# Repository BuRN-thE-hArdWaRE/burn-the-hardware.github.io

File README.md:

# E-01 Drive

This repository contains the documentation and design package for `E-01 Drive`, a hardware platform built to make PID tuning easier on real systems. The current prototype is a compact self-balancing robot style control platform built around an ESP32-S3, MPU-6050, motor driver, OLED, battery power stage, custom PCB, and mechanical chassis.

## 1. Title of the Project

`E-01 Drive: AI-Assisted PID Tuning Platform for a Self-Balancing Robot`

## 2. Problem Statement

PID controllers are widely used in robotics and embedded systems, but tuning them on real hardware is still difficult. In most student and prototype projects, tuning is done by manual trial-and-error. This wastes time, increases instability during testing, and makes it hard to reach a reliable operating point quickly.

For a self-balancing robot, the problem becomes even harder because small changes in gains can produce oscillation, overshoot, or immediate failure. A practical system is needed that can reduce the effort of selecting good PID gains while still working on real hardware.

## 3. Objective

The objective of E-01 Drive is to simplify and accelerate PID tuning by combining:

- a real embedded hardware platform,
- live sensing and motor actuation,
- a structured tuning workflow,
- and an AI-assisted tuning engine that can suggest updated gains from measured hardware responses.

The project aims to reduce manual tuning effort while improving repeatability, speed of iteration, and clarity during testing.

## 4. Existing Work

The project builds on the following common approaches already used in control engineering and robotics:

- Manual PID tuning by observing overshoot, settling time, and steady-state error.
- Classical heuristics such as Ziegler-Nichols style gain estimation.
- Simulation-first controller development before real hardware deployment.
- Adaptive and learning-based tuning methods explored in academic and industrial control systems.
- Reinforcement learning approaches for automatic controller optimization.

Within this project itself, an earlier software approach attempted TD3-based reinforcement learning for automatic PID tuning across simulated systems, but it did not produce reliable enough results for deployment on the real robot.

## 5. Gap Analysis

Existing PID tuning approaches still leave several gaps for student-built real hardware systems:

- Manual tuning is slow and highly dependent on user experience.
- Classical formulas are often too coarse for unstable or nonlinear platforms like self-balancing robots.
- Simulation-only results do not always transfer well to real hardware.
- Reinforcement learning methods can be complex to train and may fail to generalize reliably.
- Many systems do not provide a simple end-to-end workflow that connects hardware measurements directly to gain recommendations.

This gap creates a need for a practical platform that combines real hardware experimentation with a smarter iterative tuning process.

## 6. Novelty

The novelty of E-01 Drive is the combination of:

- a real self-balancing robot style hardware platform,
- a custom PCB for integrating sensing, control, motor drive, and power,
- and an AI-assisted tuning loop that uses measured hardware response data to guide PID updates.

Rather than treating PID tuning as a one-time manual setup step, the project treats tuning as an iterative data-driven workflow with both offline and online phases. This makes the prototype different from a simple balancing bot or a standard fixed-gain controller demo.

## 7. Your Project Description

E-01 Drive is a compact embedded hardware platform designed to evaluate and improve PID tuning on a real robotic system. The prototype uses:

- an ESP32-S3 development board as the main controller,
- an MPU-6050 IMU for motion sensing,
- a dual motor driver to control the two drive motors,
- an OLED display for local status output,
- a DC-DC module and battery-powered supply chain,
- a custom PCB to organize the electronics,
- and a two-wheel chassis suitable for balancing and motion-control experiments.

The control workflow is built around a self-balancing robot use case. The robot measures tilt and motion, applies PID control through the motors, and records system behavior. An external tuning service can then analyze the response and suggest better gain values. This creates a tighter loop between observation, tuning, testing, and retesting.

## 8. List of Components and the Software Used

### Hardware Components

| Component | Purpose |
| --- | --- |
| ESP32-S3 board | Main microcontroller and control execution |
| MPU-6050 IMU | Tilt and motion feedback |
| Motor driver module | Drives the left and right DC motors |
| OLED display | Local status and tuning output |
| DC-DC converter | Voltage regulation |
| Toggle switch | Power control |
| 3.7V 1200mAh battery | Portable power source |
| Two TT gear motors | Actuation |
| Two wheels | Locomotion and balance support |
| Custom PCB | Interconnect and integration platform |
| Mechanical chassis/body | Prototype structure |

### Software and Tools Used

| Software / Tool | Purpose |
| --- | --- |
| KiCad 9 | Schematic and PCB design |
| Gerber export tools | Manufacturing output generation |
| FastAPI | Backend service for tuning workflow |
| Cloud LLM tuner | Gain recommendation and adaptive tuning logic |
| SvelteKit website repo | Public project presentation and documentation |
| STEP / STL / GLB exports | 3D model sharing and fabrication references |

## 9. Methodology

The project methodology combines hardware design, embedded control, and AI-assisted tuning:

1. Design and fabricate a compact PCB for the controller, IMU, motor driver, and power modules.
2. Assemble a robot platform with two motors, wheels, battery supply, and control electronics.
3. Read tilt and motion data from the IMU using the controller.
4. Run a PID-based control loop on the hardware platform.
5. Perform exploratory hardware runs to collect response metrics.
6. Use measured values such as settling time, overshoot, steady-state error, and stability to guide gain updates.
7. Iterate until the system reaches improved behavior.

The broader tuning concept is divided into:

- `Offline tuning`: structured initial tuning using exploratory runs and recorded results.
- `Online tuning`: adaptive updates based on new disturbances or live system behavior.

## 10. Work Flow

The current project workflow can be described as:

1. Power the robot through the battery, switch, and DC-DC stage.
2. Read angle and motion feedback from the MPU-6050.
3. Execute the control loop on the ESP32-S3.
4. Drive the motors through the motor driver.
5. Observe system behavior on the hardware platform.
6. Record response metrics from each trial.
7. Send the results to the tuning workflow.
8. Receive improved PID gains.
9. Re-apply the gains on hardware and repeat.

The software architecture currently described for the tuning engine includes:

- `/init_session`
- `/answer_questions`
- `/send_results`
- `/accept`
- `/start_adaptive`
- `/breach`

These endpoints represent the offline and adaptive tuning phases of the project.

### Tuning Progress Graphs

The following graphs summarize the tuning behavior shared for this project. These repository assets were recreated from the graph screenshots provided during documentation so they can be embedded directly in the public README.

#### Kp Over Iterations

#### Steady State Over Iterations

#### Overshoot Trend During Tuning

#### PID Gains Over Iterations

## 11. Pic of the Project / Prototype

### Assembled Prototype

### Custom PCB

### Chassis and Motors

## 12. Demo Video

Software demo video file available locally: `2026-04-12 14-31-13.mkv`

Important note: the provided video file is approximately 177 MB, which exceeds GitHub's normal 100 MB file-size limit for repository commits. To complete the final submission cleanly, this video should be uploaded to a public hosting platform such as YouTube or Google Drive, and that public link should be placed here before judging.

## 13. Public GitHub Repo Deliverables

Public repository: [BuRN-thE-hArdWaRE/burn-the-hardware.github.io](https://github.com/BuRN-thE-hArdWaRE/burn-the-hardware.github.io)

### Schematics and Circuit Design

- [KiCad schematic](hardware/kicad/E-01%20Drive.kicad_sch)
- [KiCad project file](hardware/kicad/E-01%20Drive.kicad_pro)

Note: the current schematic file exists in the repository, but it is still largely incomplete and should be finished for a fully reproducible hardware submission.

### PCB Layout (KiCad Project File)

- [PCB layout](hardware/kicad/E-01%20Drive.kicad_pcb)
- [KiCad project](hardware/kicad/E-01%20Drive.kicad_pro)

### Gerber File

- [Gerber folder](hardware/gerber/team5_gerber_x2/)
- [Gerber ZIP package](hardware/gerber/team5_gerber_x2/team-5_gerber.zip)

### Source Code

- [Website source](src/)
- [Firmware and tuning architecture note](firmware/README.md)

Important note: actual firmware source files were not present in the local workspace provided for this update. This repository now includes the firmware architecture description, but the embedded source code should still be added if you want the submission to include the full software implementation.

### 3D Model With Specifications

- [STEP model](hardware/models/E-01%20Drive.step)
- [STL model](hardware/models/E-01%20Drive.stl)
- [GLB model](hardware/models/E-01%20Drive.glb)

These files provide the current 3D representation of the mechanical and hardware package available in the workspace.

## Firmware and Tuning Architecture Summary

The current tuning architecture is based on a hybrid control workflow:

- the ESP32-S3 executes the live control loop on the robot,
- the MPU-6050 provides motion feedback,
- the motor driver applies actuator output,
- and an external AI-assisted tuning service recommends PID gains from observed hardware results.

An earlier TD3 reinforcement learning approach was explored and later abandoned due to unreliable performance for real-world deployment. The current approach uses a cloud LLM with a FastAPI-based session workflow for offline and online gain adjustment.

Additional firmware notes are available in [firmware/README.md](firmware/README.md).

## Additional Project Images

### OLED Module

### IMU Module

### Motor Driver

### Power Section

### Wheels

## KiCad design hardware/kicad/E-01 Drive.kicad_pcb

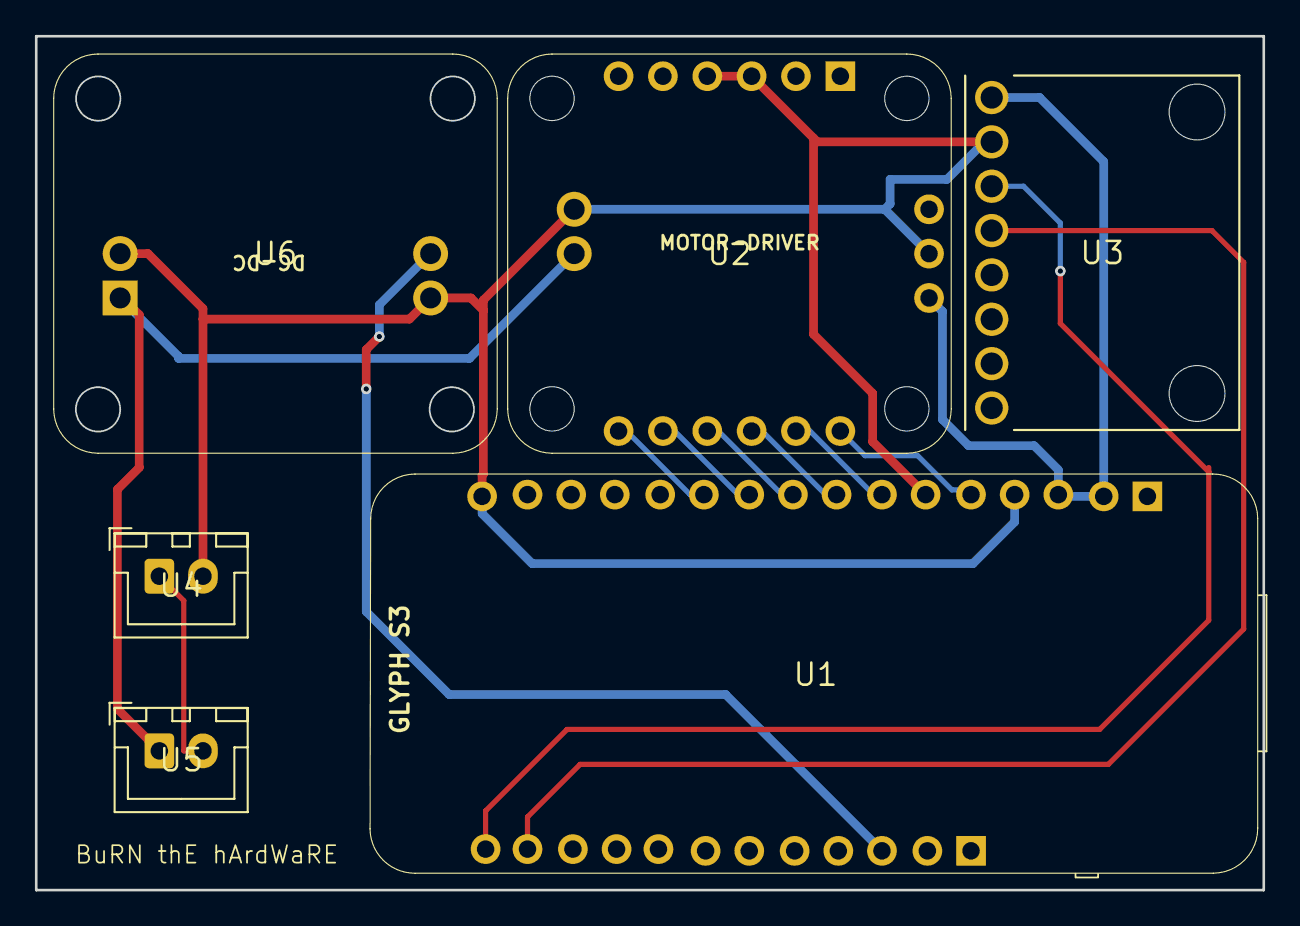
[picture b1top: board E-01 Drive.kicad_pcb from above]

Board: 2 copper layers, 70.3 x 48.9 mm, 6 parts (0 on the bottom side), 9 nets.

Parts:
U1: U1; glyph-s3
U2: U2; gmod-motor-driver
U3: U3; mpu_6050
U4: U4; JST_XH_B2B-XH-A_1x02_P2.50mm_Vertical
U5: U5; JST_XH_B2B-XH-A_1x02_P2.50mm_Vertical
U6: U6; gmod-dc-dc

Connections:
net-1: U1.10, U1.16, U1.28, U2.7, U2.16, U4.2, U5.1, U6.2, U6.3, U6.4
net-2: U4.1, U5.2
net-4: U1.14, U1.15, U2.15
net-7: U1.17, U2.14
net-8: U1.19, U2.13
net-9: U1.20, U2.12
net-10: U1.21, U2.11
net-11: U1.22, U2.10
net-12: U1.23, U2.9

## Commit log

2026-04-10 Clean up README and update project name
2026-04-10 Add 404 endpoint for fallback
2026-04-10 Add GitHub Actions workflow for GitHub Pages deployment
2026-04-10 Install adapter-static
2026-04-10 Update Node.js version from 20 to 24
2026-04-10 Update svelte.config.js so it explicitly imports vitePreprocess
2026-04-10 Fix Issues with Deployment
2026-04-12 Document E-01 Drive hardware platform
2026-04-12 Add firmware and tuning architecture description
2026-04-12 Align repo with hackathon documentation checklist
2026-04-12 Clarify demo video submission requirements
2026-04-12 Add PID tuning progress graphs to README
